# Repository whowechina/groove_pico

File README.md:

# Groove Pico - Groove Coaster Style Mini Controller
[点这里可以切换到中文版](README_CN.md)

Features:
* It's small but closely replicates the feel of the arcade controller.
* Works as a Nintendo Switch controller.
* Stereo haptic feedback.
* Command line for configurations.
* All source files open.

Thanks to many respectful guys/companies who made their tools or materials free or open source (KiCad, OnShape, InkScape, Raspberry things).

Special thanks to community developers that inspired me and helped me: CrazyRedMachine (https://github.com/CrazyRedMachine), asesidaa (https://github.com/asesidaa).

And also:
* RP_Silicon_KiCad: https://github.com/HeadBoffin/RP_Silicon_KiCad
* Type-C: https://github.com/ai03-2725/Type-C.pretty

## My Other Projects
You can check out my other cool projects.

* Popn Pico: https://github.com/whowechina/popn_pico
* IIDX Pico: https://github.com/whowechina/iidx_pico
* IIDX Teeny: https://github.com/whowechina/iidx_teeny
* Chu Pico: https://github.com/whowechina/chu_pico
* Mai Pico: https://github.com/whowechina/mai_pico
* Diva Pico: https://github.com/whowechina/diva_pico
* AIC Pico: https://github.com/whowechina/aic_pico
* Groove Pico: https://github.com/whowechina/groove_pico
* Geki Pico: https://github.com/whowechina/geki_pico
* Musec Pico: https://github.com/whowechina/musec_pico
* Ju Pico: https://github.com/whowechina/ju_pico
* Bishi Pico: https://github.com/whowechina/bishi_pico
* Bishi Pico: https://github.com/whowechina/nos_pico

## **Disclaimer** ##
I made this project in my personal time with no financial benefit or sponsorship. I will continue to improve the project. I have done my best to ensure that everything is accurate and functional, there's always a chance that mistakes may occur. I cannot be held responsible for any loss of your time or money that may result from using this open source project. Thank you for your understanding.

## About the License
It's CC-NC. So DIY for yourself and for your friend, don't make money from it. And plagiarism that doesn’t even dare to mention the original author is not acceptable. Plase note that pooling orders and group buying for raw materials is acceptable. Selling off any leftover components without profit is also acceptable.

If you're interested in buying from me, or for commercial use, please contact me (Discord, QQ group, Wechat group or leave your contact in issue section).

## My Discord Invitation
https://discord.gg/M8f2PPQFEA

## HOW TO BUILD
### PCB
* Go JLCPCB and make order with the gerber zip file (latest `Production\PCB\groove_main_xxx.zip`), regular FR-4 board, black or white color, **1.6mm** thickness.  
  
* 1x Rasberry Pico Pi Pico or pin-to-pin compatible clones (U1).  
  https://www.raspberrypi.com/products/raspberry-pi-pico
* 1x USB Type-C socket (918-418K2023S40001 or KH-TYPE-C-16P)
* 24x WS2812B-4020 side-facing RGB LEDs for the circular gimbal daughter PCBs (D20-D43).  
  https://www.lcsc.com/product-detail/Light-Emitting-Diodes-LED_Worldsemi-WS2812B-4020_C965557.html
* 19x WS2812B-3528 RGB LEDs for the main PCB (D1-D19).
* 1x 74HC4052PW, TSSOP16 package (U2).  
  https://www.lcsc.com/product-detail/Multiplexer-Demultiplexer_Nexperia-74HC4052PW_50063.html
* 2x 2N7002 SOT-23 N-Channel MOSFETs (Q1, Q2). Actually most SOT-23 package N-Channel MOSFET models will be fine.  
  https://www.nexperia.com/products/mosfets/small-signal-mosfets/2N7002.html
* 4x SH 1.25mm 3-pin connectors, both through-hole and SMD types are acceptable.  
  
* 9x 0603 0.1uF (0.1~1uF all fine) capacitors (C1 to C9), OPTIONAL but recommended.
* 2x 0603 5.1kohm resistors (R1, R2) for the USB.
* 5x 0603 10ohm resistors, (1-20ohm all work fine) (R3-R7).
* 1x LM4040A30IDBZ 3.0V shunt voltage reference (U3, SOT23-3), OPTIONAL but recommended. Model can be different, as long as it's a SOT23-3 3.0V shunt voltage reference.
* 1x 0603 100ohm resistor (R5), mandatory when U3 is present.
* 2x Kailh choc v1 switches, use light linear ones (around 35gf), such as "Red Pro".  
  
* 3x ALPS SKPMAME010 or Panasonic EVQP1K05M 6mm square tactile switches, You can use either one exclusively or a combination of both.  
  https://tech.alpsalpine.com/e/products/detail/SKPMAME010/  
  https://www3.panasonic.biz/ac/e/dl/catalog/index.jsp?series_cd=3473&part_no=EVQP1K05M
* 2x BETAFPV nano gimbals (Potentiometer, Pitch/Roll Stick). You can buy them from online RC or FPV shops. Some call "Pitch/Roll stick" as directional stick which provides auto-center for both axes.  
  https://betafpv.com/products/literadio-transmitter-nano-gimbal-for-literadio-3-and-2-se?variant=39628763529350
* 2x 1027 or 1030 DC 3V flat vibration motors.  
  https://www.amazon.com/vibration-electronic-equipment-12000RPM-adhesive/dp/B08B34W24X
* 2x M3 hex nuts.
* This is how it looks after soldering. Please note that the two circular daughter PCBs are fully wired, so you can test them before cutting them off.  

* Becareful of 3 pin holes (simplifed to 2 holes in latest version) on the top side. It's a common oversight to either forget to solder them or to leave air bubbles during the process. To avoid this, solder slowly from one side of the hole, using minimal solder wire and a generous amount of flux.  
  
* After it passes the test, you need to cut the circular daughter PCBs off.  

### 3D Printing
* Printing parameters  
  * PLA, PETG, ABS are all OK.
  * Layer height: 0.2mm
  * Support: Yes, always.

* Bottom Part: `Production\3DPrint\groove_pico_bottom.stl`, semi-transparent filament.
* Top Part: `Production\3DPrint\groove_pico_top.stl`, semi-transparent filament.
* Gimbal Stick: `Production\3DPrint\groove_pico_stick.stl`, semi-transparent filament. If you have Bambu AMS system, print the upper (above 22mm) layers with black filament.
* Gimbal Bolt: `Production\3DPrint\groove_pico_bolt.stl`, white filament.
* Gimbal Tightener: `Production\3DPrint\groove_pico_tightener.stl`, white filament.
* Button cap: `Production\3DPrint\groove_pico_button_cap.stl`, white filament, print up-side down so you get nice button surface and stem. If you have Bambu AMS system, use their special support material for the interface layer.

### Nano Gimbal Modification (Optional)
* The BETAFPV Nano Gimbals are designed for RC transmitters, the original equipped springs are a little too light for Groove Pico. If you don't like the loose feel, you can change the springs by yourself.
* I measured the original springs, they're **0.3\*3\*10mm** (means 0.3mm steel wire diameter, 3mm outter diameter, 10mm free length, the first pair from the left). So if you want a heavier feel, you can use **0.35\*3\*10mm** (the second pair from the left), **0.4\*3\*10mm** (the third pair from the left), or even **0.3\*3\*8mm** (the last pair) tension springs.  
  
* You need to unscrew all screws to replace both X and Y axis springs. The job looks difficult but after you do it once, you'll find it's not that hard.
* You may feel the gimbal a little too bouncy, especially the X axis. You can apply some damping grease to the sliding surface to reduce the bounce (put more on X-axis sliding surface). I found Type-T03 is a good choice.  

### Assembly
* Other components needed
  * 20x **M2\*4mm regular screws** to fix main PCB and daughter PCBs.
  * 20x **M2.5\*8mm regular screws** to fix the Nano Gimbals and hold bottom and top parts together.
  * 7x **10\*2** or **10\*3** (10mm diameter, 2mm or 3mm height) **self-adhesive silicone anti-slip pads** to stick to the bottom part.  
    
  * 30AWG or 32AWG ultra-thin silicone (very soft) wires, better to have them in 4 colors.  
    https://www.amazon.com/StrivedayTM-Flexible-Silicone-electronic-electrics/dp/B01KQ2JNLI?th=1

* Steps
  * Solder 4 thin silicone wires to gimbal PCBs and twist them together like a braid. It would be easier if you have different colors. My mapping is red to V, black to G, blue to LED and yellow to SW.  
    
  * Install the main PCB onto the printed base, using M2 screws.
  * Attach 2 silicone wires for each motors to the main PCB, and twist them respectively.
  * Install the BETAFPV Nano Gimbals onto the printed base part using M2.5 screws. Connect the potentiometer connectors to the main PCB.  
    
  * Install the printed bolt to the shaft for both gimbals. You need to turn the bolts until there's no screw thread and then push it to the bottom.  

  * Install the printed stick onto the shaft for both gimbals. You need to use a little force to push it in.  

  * Install the flat vibration motor and the gimbal PCB onto the stick and guide the wires through the hole. Finally, use the printed tightener and a hex nut to fix the stick.  

  * Fix the gimbal PCB to the stick using M2 screws, paying special attention to the direction.  
    
  * Solder the wires for the gimbal PCBs and motors to the corresponding pads on the main PCB. Please reserve some extra wire length for the gimbal movement. Some duct tape can be used to fix the wires on the main PCB.  

  * Now attach the printed top part to the bottom part with M2.5 screws. And apply anti-slip pads on the bottom side.  
    
  * If everything works fine, push the printed button caps onto the Choc switches and done!  

### Firmware
* UF2 file is in `Production\Firmware` folder.
* For the new build, hold the BOOTSEL button while connect the USB to a PC, there will be a disk named "RPI-RP2" showed up. Drag the UF2 firmware binary file into it. That's it. There's a small hole at the bottom side of the Groove Pico, it is facing right to the BOOTSEL button.
* If it's already running Groove Pico firmware, you can either use "update" in command line or hold down all 3 buttons while connecting to USB to enter update mode.
* To access the command line, you can use this Web Serial Terminal to connect to the USB serial port of the Groove Pico. (Note: "?" is for help)  
  https://googlechromelabs.github.io/serial-terminal/
* **NOTE:** You need to calibrate the gimbals by "gimbal calibrate" command after you flash the firmware.

### Usage
* Connect the Groove Pico to a Nintendo Switch or a PC, it will be recognized as a Switch controller.
* Buttons on top the left and right joysticks are `L` and `R`.
* There're three small aux buttons in the center, they are `B`, `SHIFT` and `A` respectively. If `SHIFT` is pressed:
  * The other two become `-` and `+`.
  * The joystick buttons become `Y` and `X`.
  * Left joystick works as `D-PAD`.

## CAD Source File
I'm using OnShape free subscription. It's powerful but it can't archive original designs to local, so I can only share the link here. STL/DXF/DWG files are exported from this online document.  
  https://cad.onshape.com/documents/97629d37ec7dd45f32c42fed/w/4cdf2d6010b5ce7b9283904a/e/c8e2720760e1863ce3a69460?renderMode=0&uiState=6693eade6539e17fa80ec4fb

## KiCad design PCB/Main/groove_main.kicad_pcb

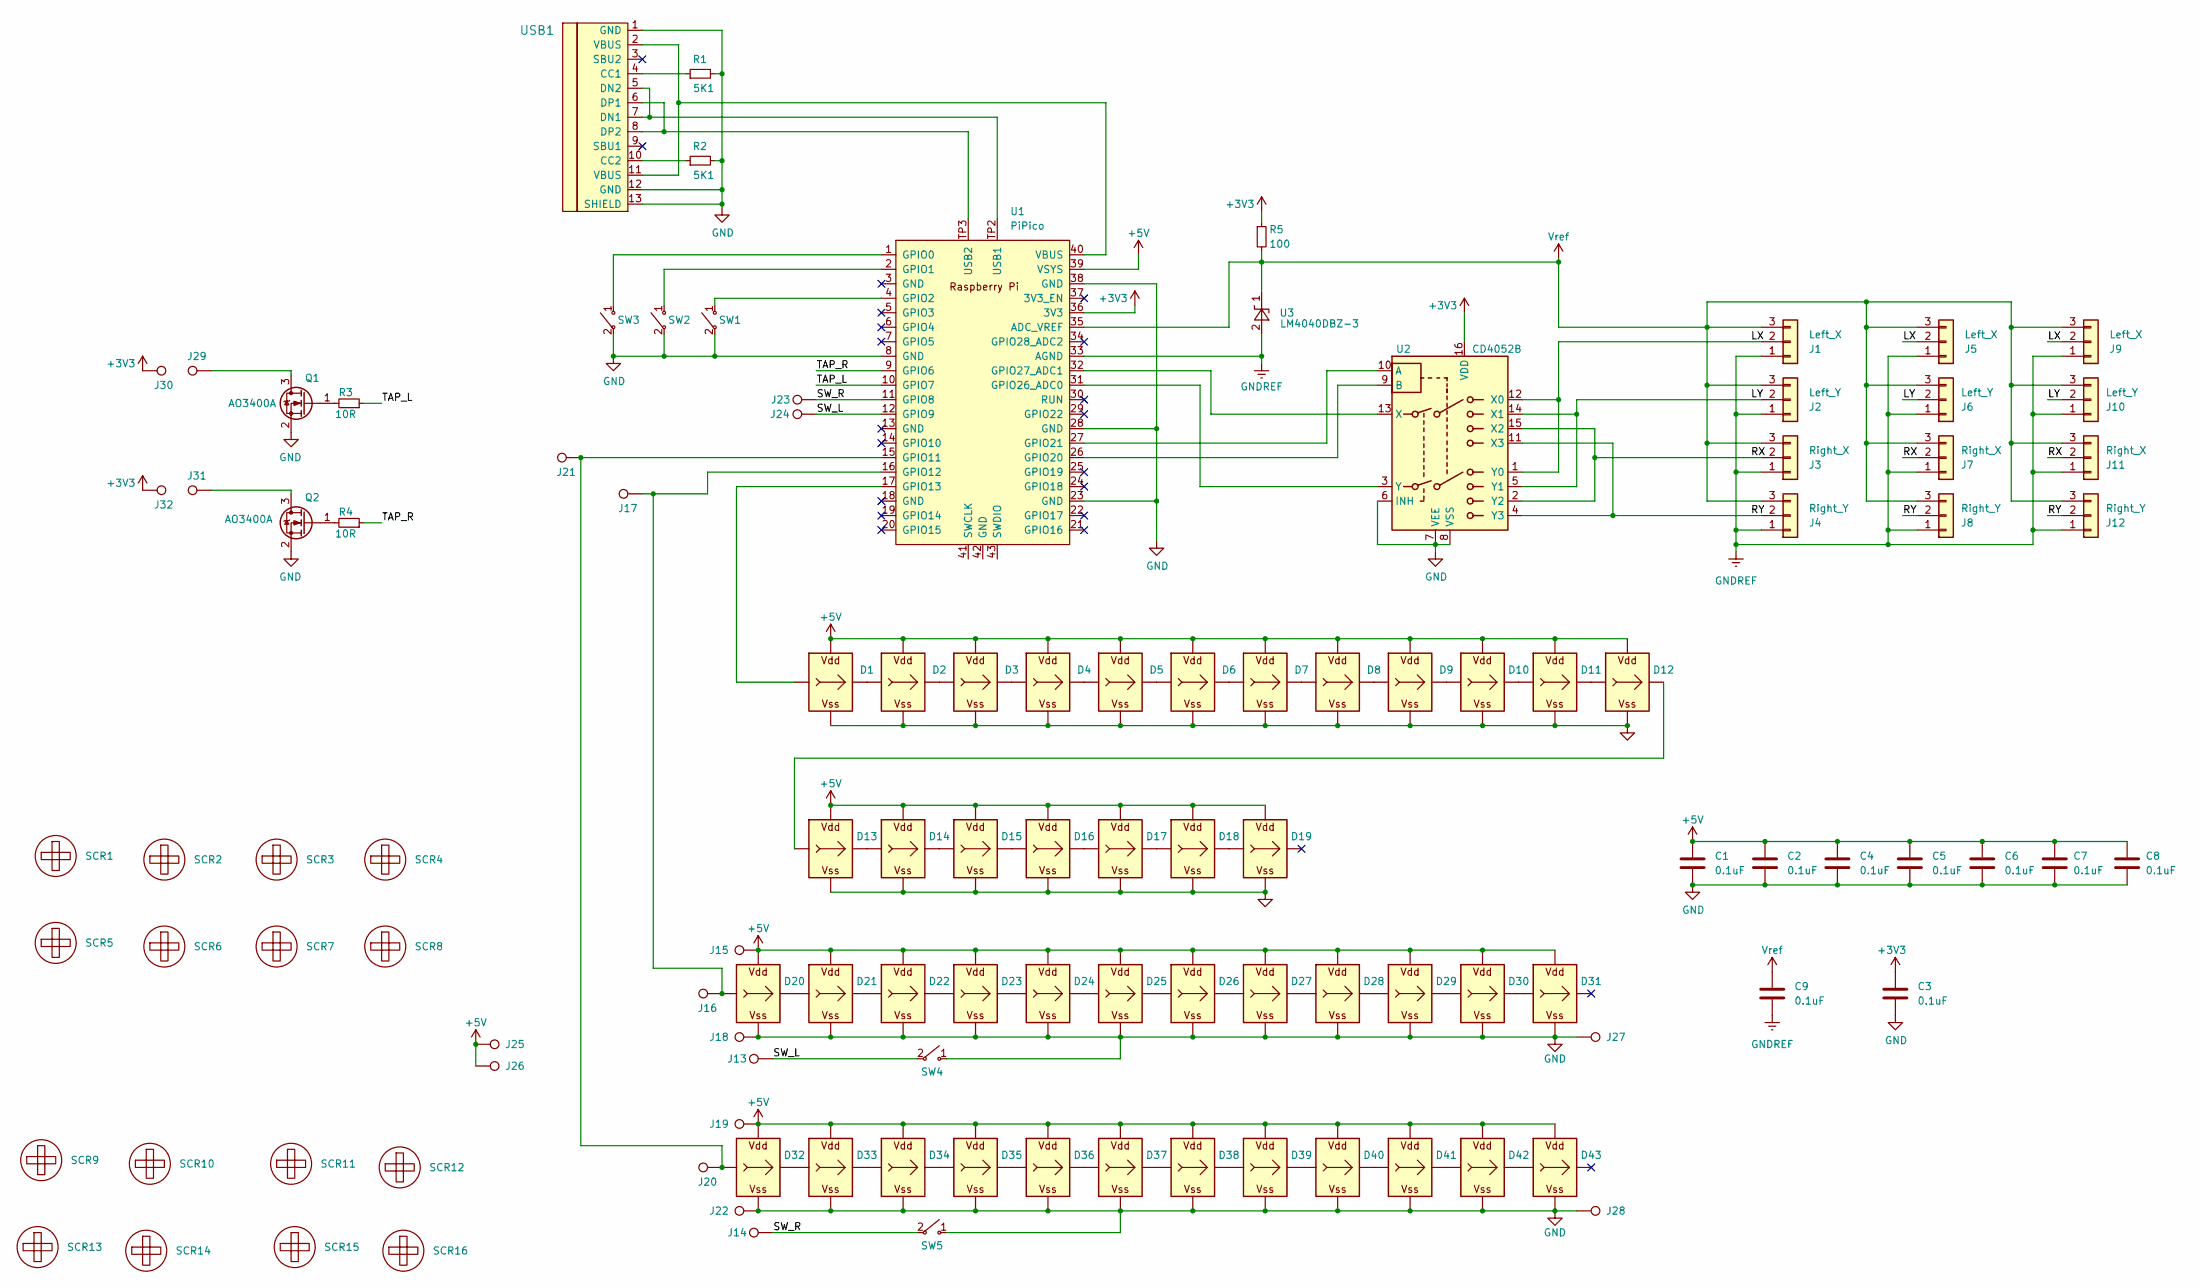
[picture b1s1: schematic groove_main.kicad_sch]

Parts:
C1, C2, C3, C4, C5, C6, C7, C8, C9: 0.1uF; C_0603_1608Metric_Pad1.08x0.95mm_HandSolder
D1, D2, D3, D4, D5, D6, D7, D8, D9, D10, D11, D12, D13, D14, D15, D16, D17, D18, D19: WS2812B_Unified; WS2812B-2835
D20, D21, D22, D23, D24, D25, D26, D27, D32, D33, D34, D35, D36, D37, D38, D39: WS2812B_Unified; WS2812B-4020
D28, D29, D30, D31, D40, D41, D42, D43: WS2812B_Unified; WS2812B-4020_UP
J1: Left_X; SH1.25_Thruhole_3P
J2: Left_Y; SH1.25_Thruhole_3P
J3: Right_X; SH1.25_Thruhole_3P
J4: Right_Y; SH1.25_Thruhole_3P
J5: Left_X; SH1.25mm_3P_SMD
J6: Left_Y; SH1.25mm_3P_SMD
J7: Right_X; SH1.25mm_3P_SMD
J8: Right_Y; SH1.25mm_3P_SMD
J9: Left_X; Solder_3P_S
J10: Left_Y; Solder_3P_S
J11: Right_X; Solder_3P_S
J12: Right_Y; Solder_3P_S
J13, J14, J23, J24: SW; Solder_1P_S
J15, J19, J25, J26, J30, J32: V; Solder_1P_S
J16, J17, J20, J21: LED; Solder_1P_S
J18, J22, J27, J28: G; Solder_1P_S
J29, J31: HAP; Solder_1P_S
Q1, Q2: AO3400A; SOT-23
R1, R2: 5K1; R_0603_1608Metric_Pad0.98x0.95mm_HandSolder; LCSC C23186
R3, R4: 10R; R_0603_1608Metric_Pad0.98x0.95mm_HandSolder; LCSC C22962
R5: 100; R_0603_1608Metric_Pad0.98x0.95mm_HandSolder; LCSC C23186
SCR1, SCR2, SCR3, SCR4, SCR5, SCR6, SCR7, SCR8, SCR9, SCR10, SCR11, SCR12, SCR13, SCR14, SCR15, SCR16: ScrewHole; Hole2.0
SW1, SW2, SW3: SWITCH_SPST; EVQP1K05M
SW4, SW5: SWITCH_SPST; SW_Kailh_Choc_V1V2_1.00u_LED
U1: PiPico; RPi_Pico_SMD_Pins
U2: CD4052B; TSSOP-16_4.4x5mm_P0.65mm
U3: LM4040DBZ-3; SOT-23
USB1: U262-161N-4BVC11; HRO-TYPE-C-31-M-12-Assembly; LCSC C319148

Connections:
+3V3: C3.1, J30.1, J32.1, R5.1, U1.36 (3V3), U2.16 (VDD)
+5V: C1.1, C2.1, C4.1, C5.1, C6.1, C7.1, C8.1, D1.V (VDD), D2.V (VDD), D3.V (VDD), D4.V (VDD), D5.V (VDD), D6.V (VDD), D7.V (VDD), D8.V (VDD), D9.V (VDD), D10.V (VDD), D11.V (VDD), D12.V (VDD), D13.V (VDD), D14.V (VDD), D15.V (VDD), D16.V (VDD), D17.V (VDD), D18.V (VDD), D19.V (VDD), D20.V (VDD), D21.V (VDD), D22.V (VDD), D23.V (VDD), D24.V (VDD), D25.V (VDD), D26.V (VDD), D27.V (VDD), D28.V (VDD), D29.V (VDD), D30.V (VDD), D31.V (VDD), D32.V (VDD), D33.V (VDD), D34.V (VDD), D35.V (VDD), D36.V (VDD), D37.V (VDD), D38.V (VDD), D39.V (VDD), D40.V (VDD), D41.V (VDD), D42.V (VDD), D43.V (VDD), J15.1, J19.1, J25.1, J26.1, U1.39 (VSYS)
/LX: J1.2, J5.2, J9.2, U2.1 (Y0), U2.12 (X0)
/LY: J2.2, J6.2, J10.2, U2.5 (Y1), U2.14 (X1)
/RX: J3.2, J7.2, J11.2, U2.2 (Y2), U2.15 (X2)
/RY: J4.2, J8.2, J12.2, U2.4 (Y3), U2.11 (X3)
/SW_L: J13.1, J24.1, SW4.2 ("~"), U1.12 (GPIO9)
/SW_R: J14.1, J23.1, SW5.2 ("~"), U1.11 (GPIO8)
/TAP_L: R3.1, U1.10 (GPIO7)
/TAP_R: R4.1, U1.9 (GPIO6)
GND: C1.2, C2.2, C3.2, C4.2, C5.2, C6.2, C7.2, C8.2, D1.G (VSS), D2.G (VSS), D3.G (VSS), D4.G (VSS), D5.G (VSS), D6.G (VSS), D7.G (VSS), D8.G (VSS), D9.G (VSS), D10.G (VSS), D11.G (VSS), D12.G (VSS), D13.G (VSS), D14.G (VSS), D15.G (VSS), D16.G (VSS), D17.G (VSS), D18.G (VSS), D19.G (VSS), D20.G (VSS), D21.G (VSS), D22.G (VSS), D23.G (VSS), D24.G (VSS), D25.G (VSS), D26.G (VSS), D27.G (VSS), D28.G (VSS), D29.G (VSS), D30.G (VSS), D31.G (VSS), D32.G (VSS), D33.G (VSS), D34.G (VSS), D35.G (VSS), D36.G (VSS), D37.G (VSS), D38.G (VSS), D39.G (VSS), D40.G (VSS), D41.G (VSS), D42.G (VSS), D43.G (VSS), J18.1, J22.1, J27.1, J28.1, Q1.2 (S), Q2.2 (S), R1.2, R2.2, SW1.2 ("~"), SW2.2 ("~"), SW3.2 ("~"), SW4.1 ("~"), SW5.1 ("~"), U1.8 (GND), U1.23 (GND), U1.28 (GND), U1.38 (GND), U2.6 (INH), U2.7 (VEE), U2.8 (VSS), USB1.1 (GND), USB1.12 (GND), USB1.13 (SHIELD)
GNDREF: C9.2, J1.1, J2.1, J3.1, J4.1, J5.1, J6.1, J7.1, J8.1, J9.1, J10.1, J11.1, J12.1, U1.33 (AGND), U3.2 (A)
unnamed: D1.I (In), U1.17 (GPIO13)
unnamed: D1.O (Out), D2.I (In)
unnamed: D2.O (Out), D3.I (In)
unnamed: D3.O (Out), D4.I (In)
unnamed: D4.O (Out), D5.I (In)
unnamed: D5.O (Out), D6.I (In)
unnamed: D6.O (Out), D7.I (In)
unnamed: D7.O (Out), D8.I (In)
unnamed: D8.O (Out), D9.I (In)
unnamed: D9.O (Out), D10.I (In)
unnamed: D10.O (Out), D11.I (In)
unnamed: D11.O (Out), D12.I (In)
unnamed: D12.O (Out), D13.I (In)
unnamed: D13.O (Out), D14.I (In)
unnamed: D14.O (Out), D15.I (In)
unnamed: D15.O (Out), D16.I (In)
unnamed: D16.O (Out), D17.I (In)
unnamed: D17.O (Out), D18.I (In)
unnamed: D18.O (Out), D19.I (In)
unnamed: D20.I (In), J16.1, J17.1, U1.16 (GPIO12)
unnamed: D20.O (Out), D21.I (In)
unnamed: D21.O (Out), D22.I (In)
unnamed: D22.O (Out), D23.I (In)
unnamed: D23.O (Out), D24.I (In)
unnamed: D24.O (Out), D25.I (In)
unnamed: D25.O (Out), D26.I (In)
unnamed: D26.O (Out), D27.I (In)
unnamed: D27.O (Out), D28.I (In)
unnamed: D28.O (Out), D29.I (In)
unnamed: D29.O (Out), D30.I (In)
unnamed: D30.O (Out), D31.I (In)
unnamed: D32.I (In), J20.1, J21.1, U1.15 (GPIO11)
unnamed: D32.O (Out), D33.I (In)
unnamed: D33.O (Out), D34.I (In)
unnamed: D34.O (Out), D35.I (In)
unnamed: D35.O (Out), D36.I (In)
unnamed: D36.O (Out), D37.I (In)
unnamed: D37.O (Out), D38.I (In)
unnamed: D38.O (Out), D39.I (In)
unnamed: D39.O (Out), D40.I (In)
unnamed: D40.O (Out), D41.I (In)
unnamed: D41.O (Out), D42.I (In)
unnamed: D42.O (Out), D43.I (In)
unnamed: J29.1, Q1.3 (D)
unnamed: Q1.1 (G), R3.2
unnamed: J31.1, Q2.3 (D)
unnamed: Q2.1 (G), R4.2
unnamed: SW3.1 ("~"), U1.1 (GPIO0)
unnamed: SW2.1 ("~"), U1.2 (GPIO1)
unnamed: SW1.1 ("~"), U1.4 (GPIO2)
unnamed: U1.26 (GPIO20), U2.9 (B)
unnamed: U1.27 (GPIO21), U2.10 (A)
unnamed: U1.31 (GPIO26_ADC0), U2.3 (Y)
unnamed: U1.32 (GPIO27_ADC1), U2.13 (X)
unnamed: U1.TP2 (USB1), USB1.5 (DN2), USB1.7 (DN1)
unnamed: U1.TP3 (USB2), USB1.6 (DP1), USB1.8 (DP2)
unnamed: U1.40 (VBUS), USB1.2 (VBUS), USB1.11 (VBUS)
unnamed: R1.1, USB1.4 (CC1)
unnamed: R2.1, USB1.10 (CC2)
Vref: C9.1, J1.3, J2.3, J3.3, J4.3, J5.3, J6.3, J7.3, J8.3, J9.3, J10.3, J11.3, J12.3, R5.2, U1.35 (ADC_VREF), U3.1 (K)

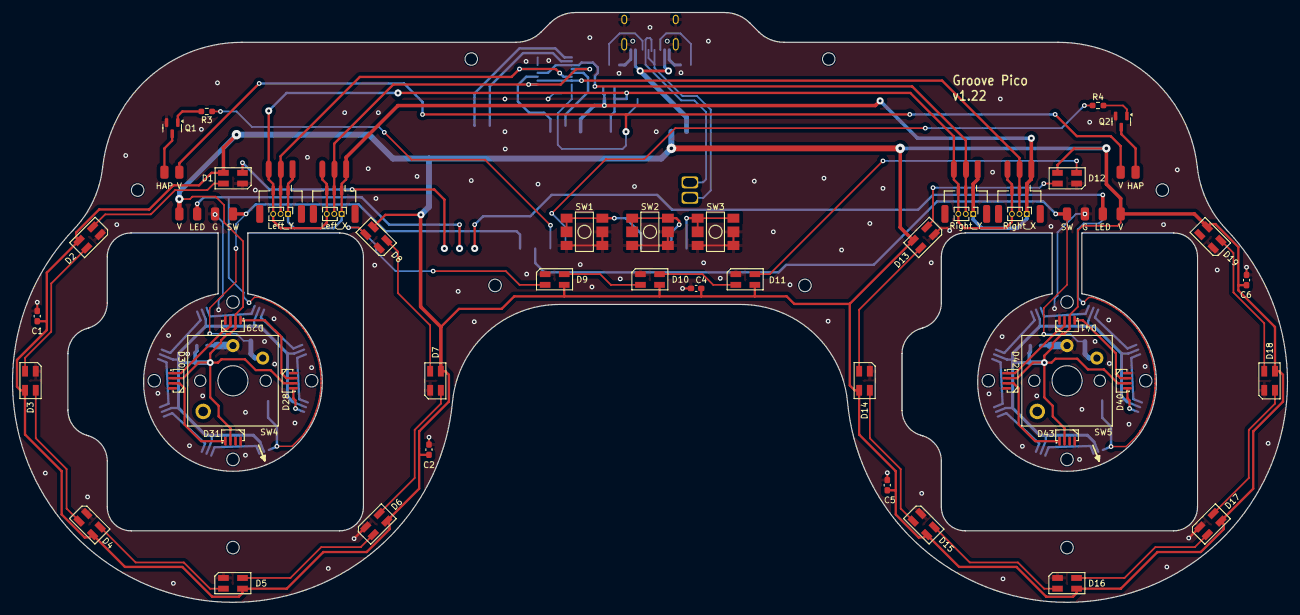
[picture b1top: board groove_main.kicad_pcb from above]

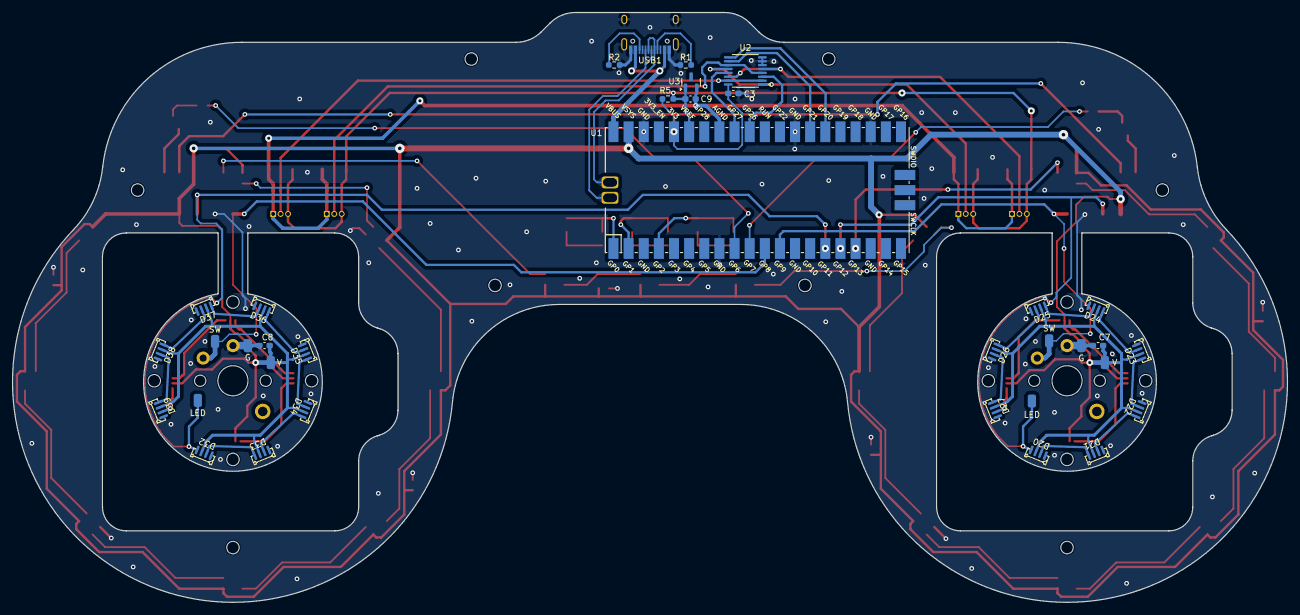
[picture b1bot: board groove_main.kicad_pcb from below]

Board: 2 copper layers, 214.0 x 99.0 mm, 116 parts (35 on the bottom side), 72 nets.

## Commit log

2024-06-26 Gimbal PCB v1.0
2024-06-30 Main PCB in progress (20%)
2024-06-30 Main PCB progress 50%
2024-06-30 Main PCB progress 70%
2024-07-01 Main PCB progress 85%
2024-07-02 Main PCB v1.0
2024-07-03 Initial firmware submit
2024-07-05 Basic gimbal reading
2024-07-05 Basic ws2812 based light driver
2024-07-07 Firmware roughly working on a Switch
2024-07-08 Gimbal calibration
2024-07-09 Add haptic feedback
2024-07-09 Better gimbal reading
2024-07-09 Add slots in PCB for Hall gimbals
2024-07-10 Main PCB v1.1
2024-07-10 CLI welcome
2024-07-10 Save cleanup and magic change
2024-07-12 Base light effect
2024-07-12 Shorten gimbal calibration time
2024-07-13 Steering light is there.
2024-07-13 Optimize smd jst connector footprint
2024-07-13 Better lighting (hoping)
2024-07-14 PCB v1.2 (easier USB soldering holes)
2024-07-14 Remove gimbal PCB
2024-07-14 Some defaults change
2024-07-14 Readme (EN) 70%
2024-07-15 Readme (EN) done
2024-07-15 Upload STL files
2024-07-15 Put some base color to the body
2024-07-15 Fix format issue on GitHub page
2024-07-15 Still trying to fix GitHub markdown rendering issue
2024-07-15 Hope this is the last markdown fix
2024-07-15 Better cross-reference
2024-07-15 Correcting gimbal axis direction
2024-07-16 Light color defined by config
2024-07-16 Light color configurable
2024-07-16 Haptics can be disabled
2024-07-16 Nano gimbal tension spring mod
2024-07-18 Damping grease advices
2024-07-19 README CN version done
2024-07-19 Fix a typo
2024-09-05 Thanks to some projects
2024-10-02 Cross-reference and license update
2024-10-18 Cross-reference and Discord invitation
2024-11-23 Cross-reference
2024-11-23 Fix a color assignment bug
2024-11-24 Explaining button assignment
2024-12-01 Fix getchar return handling
2024-12-01 Improve screw holes
2024-12-07 PCB v1.21 (easier soldering)
2025-01-03 nkro and 1000 fps for core 0
2025-01-03 Fix brightness control
2025-01-04 Use a better polling rate
2025-01-19 Send HID report only when status changes
2025-04-04 Cross-reference to new projects
2025-06-10 Improve voltage reference design
2025-06-11 More switch keys when "ALT" is pressed
